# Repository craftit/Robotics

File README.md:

# Robotics
This is a general scratch area for my robotics projects. One things are in decent shape I will organise and move them more appropriate.

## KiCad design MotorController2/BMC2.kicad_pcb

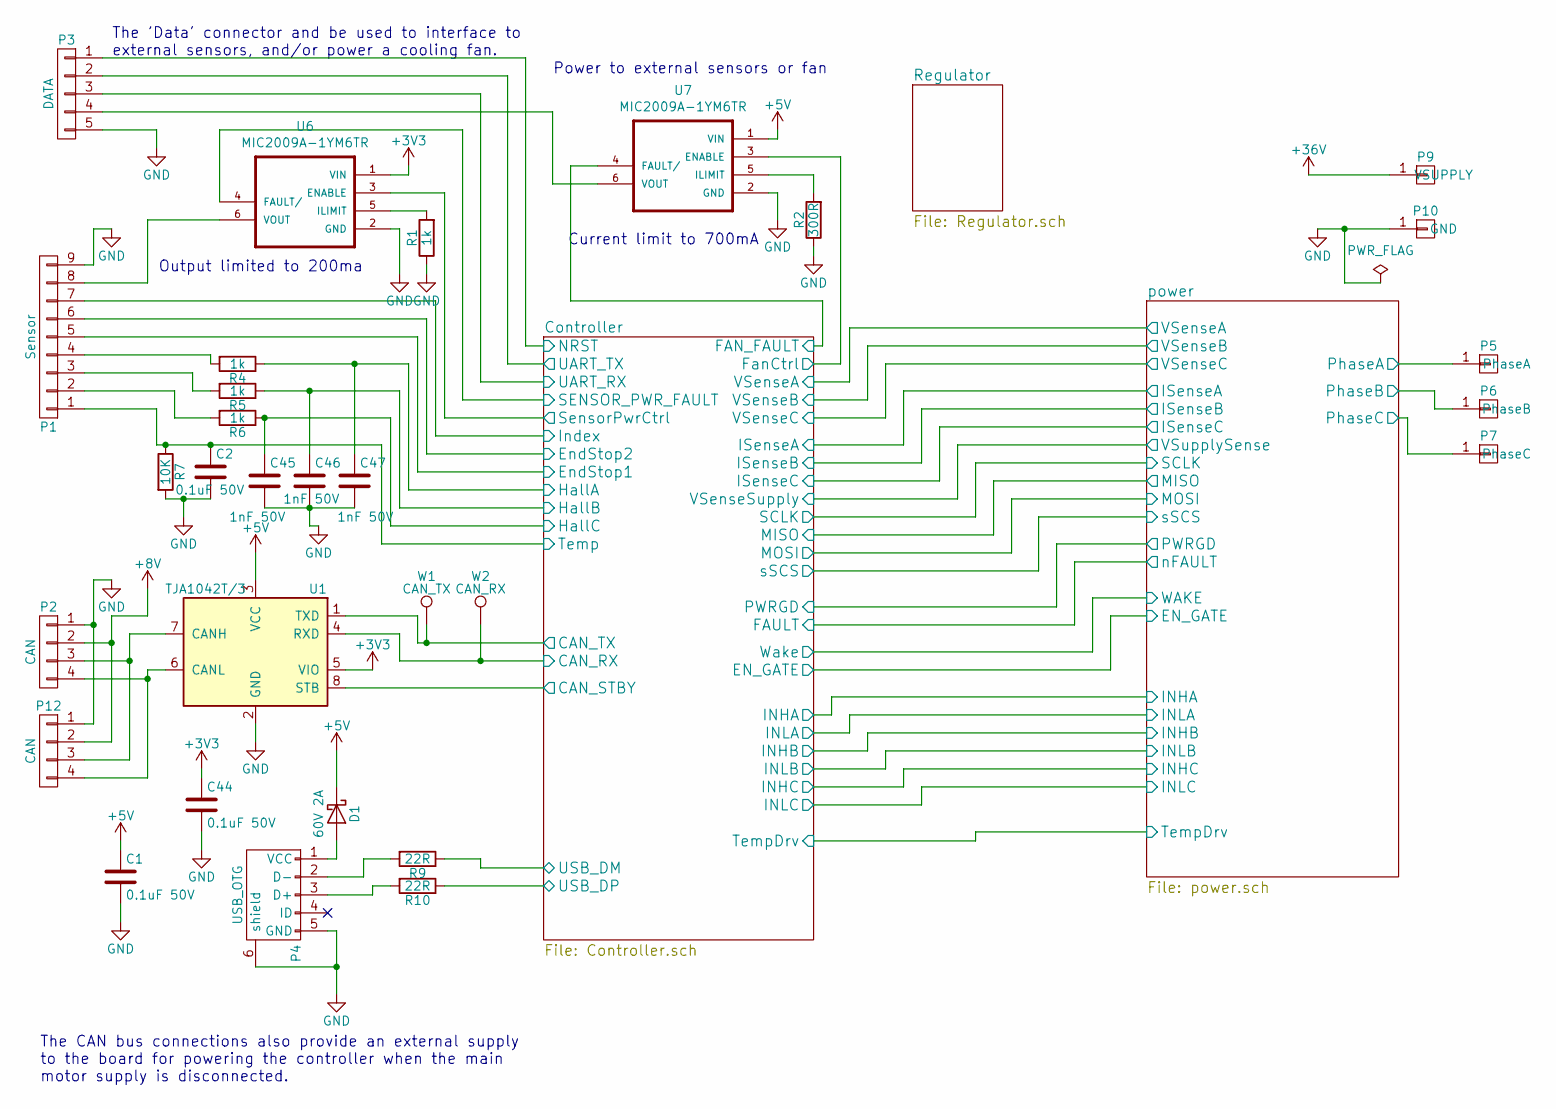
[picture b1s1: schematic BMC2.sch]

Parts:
C1: 0.1uF 50V; C_0805_HandSoldering; Farnell 1759265
C2, C44: 0.1uF 50V; C_0805_HandSoldering
C45, C46, C47: 1nF 50V; C_0805_HandSoldering; Farnell 9406344
D1: 60V 2A; SOD-123; Farnell 2284958
P1: Sensor; Pin_Header_Angled_1x09; Farnell 2468365
P2, P12: CAN; Pin_Header_Angled_1x04; Farnell 588738
P3: DATA; Pin_Header_Angled_1x05; Farnell 588740
P4: USB_OTG; USB_Mini-B; Farnell 1125348
P5: PhaseA; 1pin
P6: PhaseB; 1pin
P7: PhaseC; 1pin
P9: VSUPPLY; 1pin
P10: GND; 1pin
R1, R5, R6: 1k; R_0805_HandSoldering
R2: 300R; R_0805_HandSoldering; Farnell 2447633
R4: 1k; R_0805_HandSoldering; Farnell 2447587
R7: 10K; R_0805_HandSoldering; Farnell 2447553
R9: 22R; R_0805_HandSoldering; Farnell 2447609
R10: 22R; R_0805_HandSoldering
U1: TJA1042T/3; SOIC-8_3.9x4.9mm_Pitch1.27mm; Farnell 2574957
U6: MIC2009A-1YM6TR; SOT-23-6; Farnell 2509888
U7: MIC2009A-1YM6TR; SOT-23-6
W1: CAN_TX; Measurement_Point_Round-SMD-Pad_Small
W2: CAN_RX; Measurement_Point_Round-SMD-Pad_Small

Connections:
+3V3: C44.1, U1.5 (VIO), U6.1 (VIN); also elsewhere on the board
+5V: C1.1, D1.1 (K), U1.3 (VCC), U7.1 (VIN); also elsewhere on the board
+8V: P2.2, P12.2; also elsewhere on the board
+36V: P9.1; also elsewhere on the board
/Controller/CAN_RX: U1.4 (RXD), W2.1; also elsewhere on the board
/Controller/CAN_STBY: U1.8 (STB); also elsewhere on the board
/Controller/CAN_TX: U1.1 (TXD), W1.1; also elsewhere on the board
/Controller/EndStop1: P1.5; also elsewhere on the board
/Controller/EndStop2: P1.6; also elsewhere on the board
/Controller/FAN_FAULT: U7.4 (FAULT/); also elsewhere on the board
/Controller/FanCtrl: U7.3 (ENABLE); also elsewhere on the board
/Controller/HallA: C47.1, R4.1; also elsewhere on the board
/Controller/HallB: C46.1, R5.1; also elsewhere on the board
/Controller/HallC: C45.1, R6.1; also elsewhere on the board
/Controller/Index: P1.7; also elsewhere on the board
/Controller/SENSOR_PWR_FAULT: U6.4 (FAULT/); also elsewhere on the board
/Controller/SensorPwrCtrl: U6.3 (ENABLE); also elsewhere on the board
/Controller/Temp: C2.1, P1.1, R7.1; also elsewhere on the board
/Controller/UART_RX: P3.3; also elsewhere on the board
/Controller/UART_TX: P3.2; also elsewhere on the board
/Controller/USB_DM: R9.1; also elsewhere on the board
/Controller/USB_DP: R10.1; also elsewhere on the board
/power/PhaseA: P5.1; also elsewhere on the board
/power/PhaseB: P6.1; also elsewhere on the board
/power/PhaseC: P7.1; also elsewhere on the board
GND: C1.2, C2.2, C44.2, C45.2, C46.2, C47.2, P1.9, P2.1, P3.5, P4.5 (GND), P4.6 (shield), P10.1, P12.1, R1.1, R2.1, R7.2, U1.2 (GND), U6.2 (GND), U7.2 (GND); also elsewhere on the board
NRST: P3.1; also elsewhere on the board
unnamed: D1.2 (A), P4.1 (VCC)
unnamed: P1.2, R6.2
unnamed: P1.3, R5.2
unnamed: P1.4, R4.2
unnamed: P1.8, U6.6 (VOUT)
unnamed: P3.4, U7.6 (VOUT)
unnamed: P4.2 (D-), R9.2
unnamed: P4.3 (D+), R10.2
unnamed: P2.3, P12.3, U1.7 (CANH)
unnamed: P2.4, P12.4, U1.6 (CANL)
unnamed: R1.2, U6.5 (ILIMIT)
unnamed: R2.2, U7.5 (ILIMIT)

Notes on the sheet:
Output limited to 200ma
Current limit to 700mA
Power to external sensors or fan
The CAN bus connections also provide an external supply to the board for powering the controller when the main motor supply is disconnected.
The 'Data' connector and be used to interface to external sensors, and/or power a cooling fan.

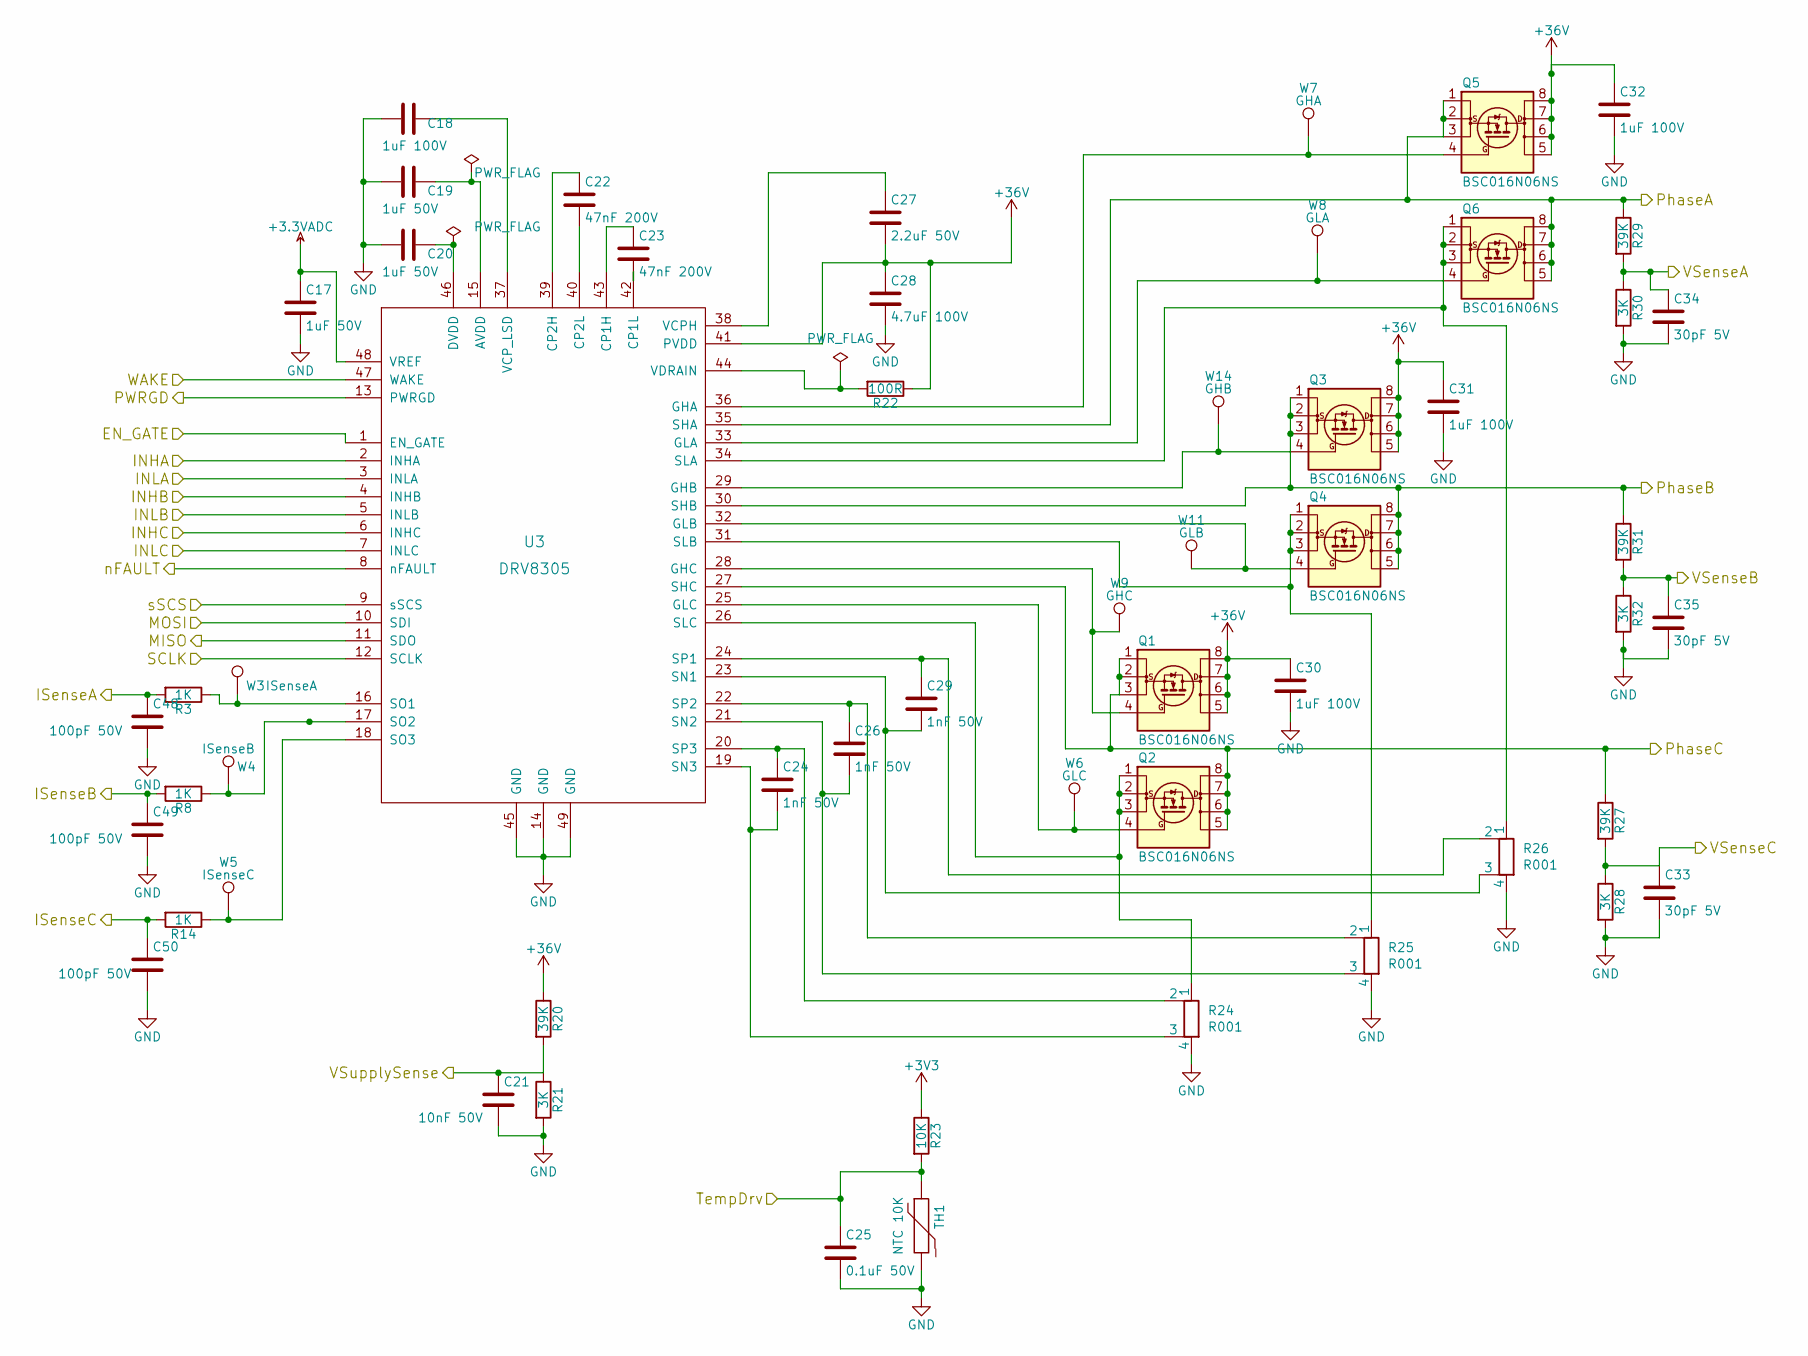
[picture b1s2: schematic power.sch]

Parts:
C17, C19, C20: 1uF 50V; C_0805_HandSoldering
C18, C30, C31, C32: 1uF 100V; C_1206_HandSoldering; Farnell 2320876
C21: 10nF 50V; C_0805_HandSoldering; Farnell 1414662
C22, C23: 47nF 200V; C_1206_HandSoldering; Farnell 1855874
C24, C26, C29: 1nF 50V; C_0805_HandSoldering; Farnell 9406344
C25: 0.1uF 50V; C_0805_HandSoldering
C27: 2.2uF 50V; C_1206_HandSoldering; Farnell 1288208
C28: 4.7uF 100V; C_1206_HandSoldering; Farnell 2310265
C33, C34, C35: 30pF 5V; C_0805_HandSoldering; Farnell 2581093
C48: 100pF 50V; C_0805_HandSoldering; Farnell 1759203
C49, C50: 100pF 50V; C_0805_HandSoldering
Q1, Q2, Q3, Q4, Q6: BSC016N06NS; SON127P532X615X110-8N
Q5: BSC016N06NS; SON127P532X615X110-8N; Farnell2 2432702
R3, R8, R14: 1K; R_0805_HandSoldering
R20, R27, R31: 39K; R_0805_HandSoldering
R21, R28, R32: 3K; R_0805_HandSoldering
R22: 100R; R_0805_HandSoldering; Farnell 2447552
R23: 10K; R_0805_HandSoldering
R24, R25: R001; R_PSR400_SENSE
R26: R001; R_PSR400_SENSE; Farnell 2475107
R29: 39K; R_0805_HandSoldering; Farnell 2447646
R30: 3K; R_0805_HandSoldering; Farnell 2073731
TH1: NTC 10K; R_0805_HandSoldering; Farnell 2103179
U3: DRV8305; QFP50P900X900X120-49N; Farnell 2611246
W3: ISenseA; Measurement_Point_Round-SMD-Pad_Small
W4: ISenseB; Measurement_Point_Round-SMD-Pad_Small
W5: ISenseC; Measurement_Point_Round-SMD-Pad_Small
W6: GLC; Measurement_Point_Round-SMD-Pad_Small
W7: GHA; Measurement_Point_Round-SMD-Pad_Small
W8: GLA; Measurement_Point_Round-SMD-Pad_Small
W9: GHC; Measurement_Point_Round-SMD-Pad_Small
W11: GLB; Measurement_Point_Round-SMD-Pad_Small
W14: GHB; Measurement_Point_Round-SMD-Pad_Small

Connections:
+3.3VADC: C17.1, U3.48 (VREF); also elsewhere on the board
+3V3: R23.1; also elsewhere on the board
+36V: C27.2, C28.1, C30.1, C31.1, C32.1, Q1.5 (D), Q1.6 (D), Q1.7 (D), Q1.8 (D), Q3.5 (D), Q3.6 (D), Q3.7 (D), Q3.8 (D), Q5.5 (D), Q5.6 (D), Q5.7 (D), Q5.8 (D), R20.1, R22.1, U3.41 (PVDD); also elsewhere on the board
/Controller/EN_GATE: U3.1 (EN_GATE); also elsewhere on the board
/Controller/FAULT: U3.8 (nFAULT); also elsewhere on the board
/Controller/INHA: U3.2 (INHA); also elsewhere on the board
/Controller/INHB: U3.4 (INHB); also elsewhere on the board
/Controller/INHC: U3.6 (INHC); also elsewhere on the board
/Controller/INLA: U3.3 (INLA); also elsewhere on the board
/Controller/INLB: U3.5 (INLB); also elsewhere on the board
/Controller/INLC: U3.7 (INLC); also elsewhere on the board
/Controller/ISenseA: C48.1, R3.2; also elsewhere on the board
/Controller/ISenseB: C49.1, R8.2; also elsewhere on the board
/Controller/ISenseC: C50.1, R14.2; also elsewhere on the board
/Controller/MISO: U3.11 (SDO); also elsewhere on the board
/Controller/MOSI: U3.10 (SDI); also elsewhere on the board
/Controller/PWRGD: U3.13 (PWRGD); also elsewhere on the board
/Controller/SCLK: U3.12 (SCLK); also elsewhere on the board
/Controller/TempDrv: C25.1, R23.2, TH1.1; also elsewhere on the board
/Controller/VSenseA: C34.1, R29.2, R30.1; also elsewhere on the board
/Controller/VSenseB: C35.1, R31.2, R32.1; also elsewhere on the board
/Controller/VSenseC: C33.1, R27.2, R28.1; also elsewhere on the board
/Controller/VSenseSupply: C21.1, R20.2, R21.1; also elsewhere on the board
/Controller/sSCS: U3.9 (sSCS); also elsewhere on the board
/power/PhaseA: Q5.1 (S), Q5.2 (S), Q5.3 (S), Q6.5 (D), Q6.6 (D), Q6.7 (D), Q6.8 (D), R29.1, U3.35 (SHA); also elsewhere on the board
/power/PhaseB: Q3.1 (S), Q3.2 (S), Q3.3 (S), Q4.5 (D), Q4.6 (D), Q4.7 (D), Q4.8 (D), R31.1, U3.30 (SHB); also elsewhere on the board
/power/PhaseC: Q1.1 (S), Q1.2 (S), Q1.3 (S), Q2.5 (D), Q2.6 (D), Q2.7 (D), Q2.8 (D), R27.1, U3.27 (SHC); also elsewhere on the board
/power/WAKE: U3.47 (WAKE); also elsewhere on the board
GND: C17.2, C18.2, C19.2, C20.2, C21.2, C25.2, C28.2, C30.2, C31.2, C32.2, C33.2, C34.2, C35.2, C48.2, C49.2, C50.2, R21.2, R24.4, R25.4, R26.4, R28.2, R30.2, R32.2, TH1.2, U3.14 (GND), U3.45 (GND), U3.49 (GND); also elsewhere on the board
unnamed: C18.1, U3.37 (VCP_LSD)
unnamed: C19.1, U3.15 (AVDD)
unnamed: C20.1, U3.46 (DVDD)
unnamed: C22.1, U3.39 (CP2H)
unnamed: C22.2, U3.40 (CP2L)
unnamed: C23.1, U3.43 (CP1H)
unnamed: C23.2, U3.42 (CP1L)
unnamed: C24.1, R24.2, U3.20 (SP3)
unnamed: C24.2, R24.3, U3.19 (SN3)
unnamed: C26.1, R25.2, U3.22 (SP2)
unnamed: C26.2, R25.3, U3.21 (SN2)
unnamed: C27.1, U3.38 (VCPH)
unnamed: C29.1, R26.2, U3.24 (SP1)
unnamed: C29.2, R26.3, U3.23 (SN1)
unnamed: Q1.4 (G), U3.28 (GHC), W9.1
unnamed: Q2.1 (S), Q2.2 (S), Q2.3 (S), R24.1, U3.26 (SLC)
unnamed: Q2.4 (G), U3.25 (GLC), W6.1
unnamed: Q3.4 (G), U3.29 (GHB), W14.1
unnamed: Q4.1 (S), Q4.2 (S), Q4.3 (S), R25.1, U3.31 (SLB)
unnamed: Q4.4 (G), U3.32 (GLB), W11.1
unnamed: Q5.4 (G), U3.36 (GHA), W7.1
unnamed: Q6.1 (S), Q6.2 (S), Q6.3 (S), R26.1, U3.34 (SLA)
unnamed: Q6.4 (G), U3.33 (GLA), W8.1
unnamed: R3.1, U3.16 (SO1), W3.1
unnamed: R8.1, U3.17 (SO2), W4.1
unnamed: R14.1, U3.18 (SO3), W5.1
unnamed: R22.2, U3.44 (VDRAIN)

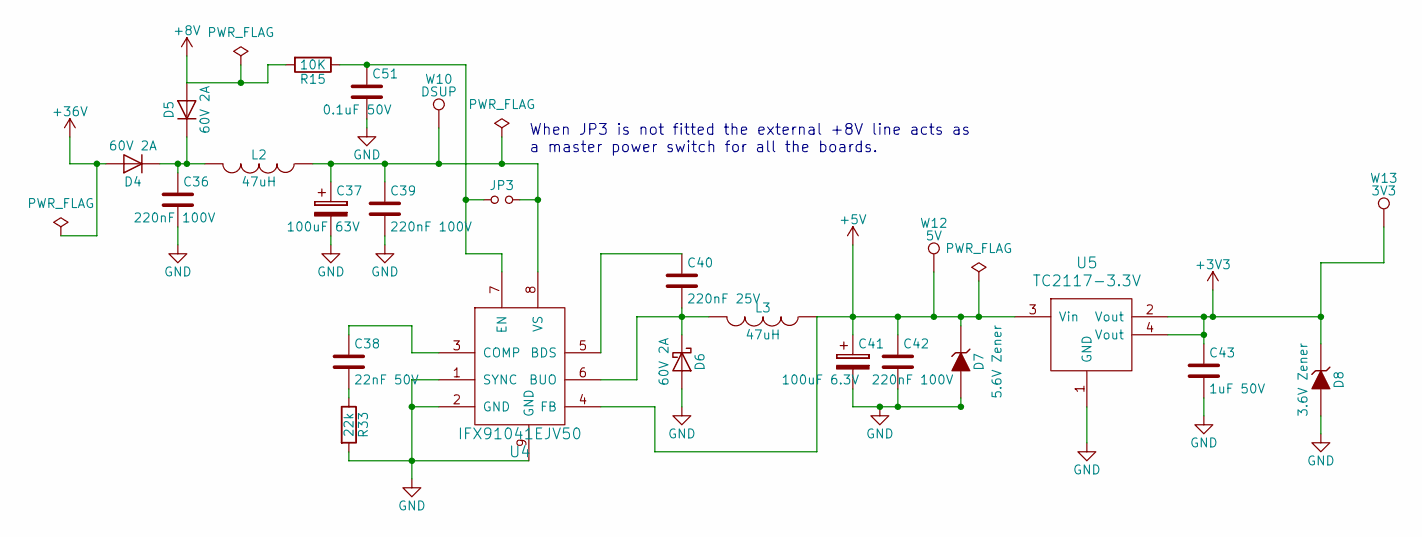
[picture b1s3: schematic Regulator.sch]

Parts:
C36, C39: 220nF 100V; C_1206_HandSoldering; Farnell 1856615
C37: 100uF 63V; c_elec_10x10.5; Farnell 9696040
C38: 22nF 50V; C_0805_HandSoldering; Farnell 1414682
C40: 220nF 25V; C_0805_HandSoldering; Farnell 1856615
C41: 100uF 6.3V; c_elec_6.3x5.8; Farnell 2611349
C42: 220nF 100V; C_0805_HandSoldering; Farnell 1856615
C43: 1uF 50V; C_0805_HandSoldering
C51: 0.1uF 50V; C_0805_HandSoldering
D4: 60V 2A; SOD-123
D5, D6: 60V 2A; SOD-123; Farnell 2284958
D7: 5.6V Zener; SOD-123; Part MMSZ4690T1G; Farnell 1459122
D8: 3.6V Zener; SOD-123; Part MMSZ5227B; Farnell 1700854
JP3: Jumper_NO_Small; R_0805_HandSoldering
L2: 47uH; SELF-WE-PD3S; Farnell 2345091
L3: 47uH; SELF-WE-PD3S
R15: 10K; R_0805_HandSoldering
R33: 22k; R_0805_HandSoldering; Farnell 9238646
U4: IFX91041EJV50; SOIC-8-1EP_3.9x4.9mm_Pitch1.27mm; Farnell 2432504
U5: TC2117-3.3V; SOT-223; Farnell 1605581
W10: DSUP; Measurement_Point_Round-SMD-Pad_Small
W12: 5V; Measurement_Point_Round-SMD-Pad_Small
W13: 3V3; Measurement_Point_Round-SMD-Pad_Small

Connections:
+3V3: C43.1, D8.1 (K), U5.2 (Vout), U5.4 (Vout), W13.1; also elsewhere on the board
+5V: C41.1, C42.1, D7.1 (K), L3.1, U4.4 (FB), U5.3 (Vin), W12.1; also elsewhere on the board
+8V: D5.2 (A), R15.2; also elsewhere on the board
+36V: D4.2 (A); also elsewhere on the board
GND: C36.2, C37.2, C39.2, C41.2, C42.2, C43.2, C51.2, D6.2 (A), D7.2 (A), D8.2 (A), R33.2, U4.1 (SYNC), U4.2 (GND), U4.9 (GND), U5.1 (GND); also elsewhere on the board
unnamed: C36.1, D4.1 (K), D5.1 (K), L2.2
unnamed: C37.1, C39.1, JP3.2, L2.1, U4.8 (VS), W10.1
unnamed: C38.1, U4.3 (COMP)
unnamed: C38.2, R33.1
unnamed: C40.1, U4.5 (BDS)
unnamed: C40.2, D6.1 (K), L3.2, U4.6 (BUO)
unnamed: C51.1, JP3.1, R15.1, U4.7 (EN)

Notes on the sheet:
When JP3 is not fitted the external +8V line acts as a master power switch for all the boards.

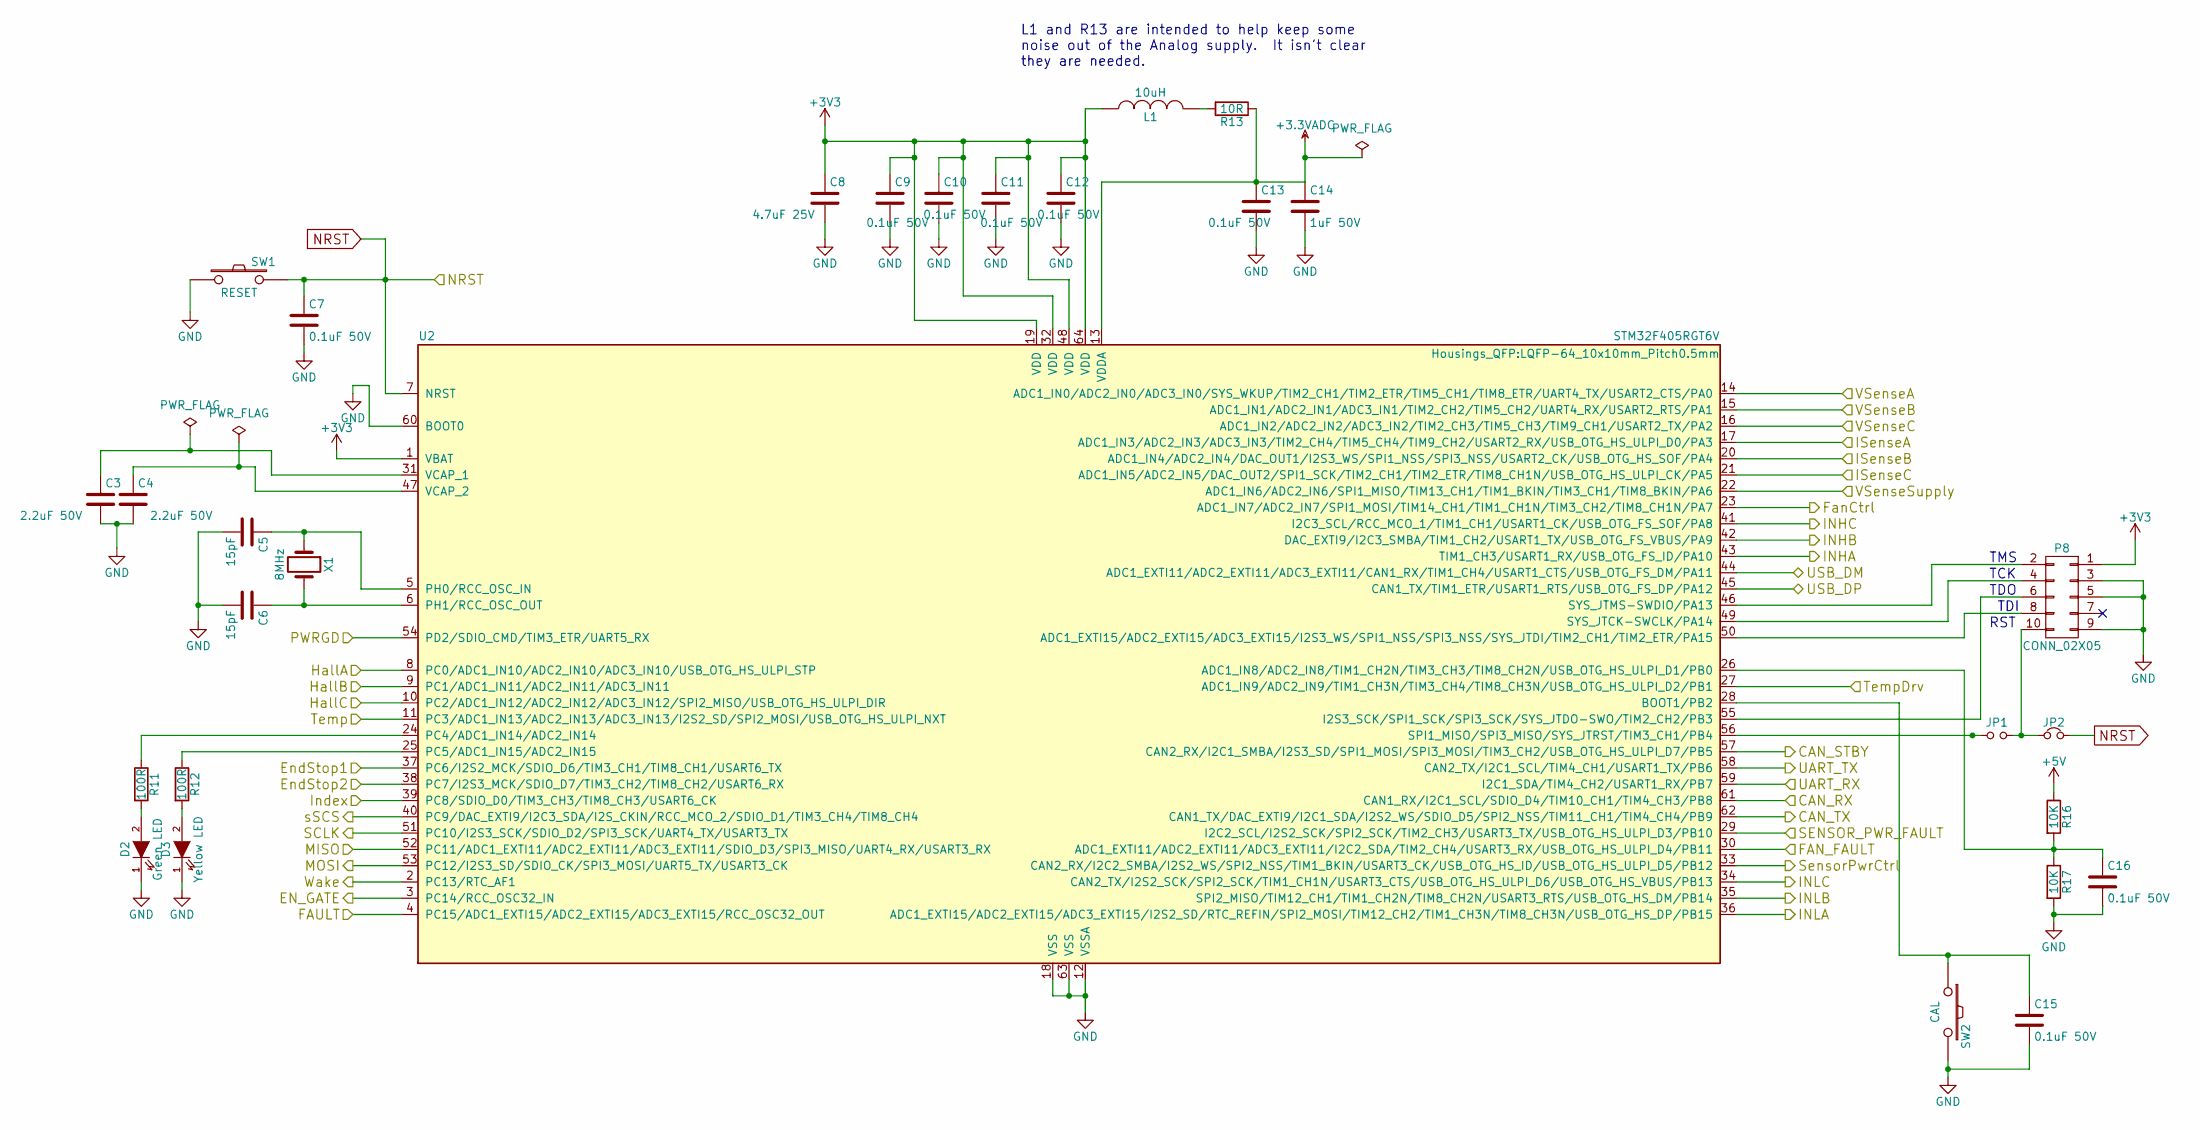
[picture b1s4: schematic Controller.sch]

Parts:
C3, C4: 2.2uF 50V; C_0805_HandSoldering; Farnell 2611933
C5: 15pF; C_0805_HandSoldering; Farnell 2497014
C6: 15pF; C_0805_HandSoldering
C7, C9, C10, C11, C12, C13, C15, C16: 0.1uF 50V; C_0805_HandSoldering
C8: 4.7uF 25V; C_1206_HandSoldering; Farnell 9227938
C14: 1uF 50V; C_0805_HandSoldering; Farnell 1759432
D2: Green LED; LED_0805; Farnell 1465996
D3: Yellow LED; LED_0805; Farnell 1581241
JP1: Jumper_NO_Small; R_0805_HandSoldering
JP2: Jumper_NC_Small; R_0805_HandSoldering; Farnell 9333681
L1: 10uH; R_0805_HandSoldering; Farnell 2215650
P8: CONN_02X05; SMT-HDR-10
R11, R12: 100R; R_0805_HandSoldering
R13: 10R; R_0805_HandSoldering; Farnell 2447556
R16, R17: 10K; R_0805_HandSoldering
SW1: RESET; SW_SPST_FSMSM; Farnell 2468741
SW2: CAL; SW_SPST_FSMSM; Farnell 2468741
U2: STM32F405RGT6V; LQFP-64_10x10mm_Pitch0.5mm; Farnell 2333282
X1: 8MHz; ABM3; Farnell 2101329

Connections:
+3.3VADC: C13.1, C14.1, R13.1, U2.13 (VDDA); also elsewhere on the board
+3V3: C8.1, C9.1, C10.1, C11.1, C12.1, L1.1, P8.1, U2.1 (VBAT), U2.19 (VDD), U2.32 (VDD), U2.48 (VDD), U2.64 (VDD); also elsewhere on the board
+5V: R16.1; also elsewhere on the board
/Controller/CAN_RX: U2.61 (CAN1_RX/I2C1_SCL/SDIO_D4/TIM10_CH1/TIM4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); also elsewhere on the board
/Controller/CAN_STBY: U2.57 (CAN2_RX/I2C1_SMBA/I2S3_SD/SPI1_MOSI/SPI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); also elsewhere on the board
/Controller/CAN_TX: U2.62 (CAN1_TX/DAC_EXTI9/I2C1_SDA/I2S2_WS/SDIO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); also elsewhere on the board
/Controller/EN_GATE: U2.3 (PC14/RCC_OSC32_IN); also elsewhere on the board
/Controller/EndStop1: U2.37 (PC6/I2S2_MCK/SDIO_D6/TIM3_CH1/TIM8_CH1/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); also elsewhere on the board
/Controller/EndStop2: U2.38 (PC7/I2S3_MCK/SDIO_D7/TIM3_CH2/TIM8_CH2/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); also elsewhere on the board
/Controller/FAN_FAULT: U2.30 (ADC1_EXTI11/ADC2_EXTI11/ADC3_EXTI11/I2C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); also elsewhere on the board
/Controller/FAULT: U2.4 (PC15/ADC1_EXTI15/ADC2_EXTI15/ADC3_EXTI1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); also elsewhere on the board
/Controller/FanCtrl: U2.23 (ADC1_IN7/ADC2_IN7/SPI1_MOSI/TIM14_CH1/T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); also elsewhere on the board
/Controller/HallA: U2.8 (PC0/ADC1_IN10/ADC2_IN10/ADC3_IN10/USB_O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); also elsewhere on the board
/Controller/HallB: U2.9 (PC1/ADC1_IN11/ADC2_IN11/ADC3_IN11); also elsewhere on the board
/Controller/HallC: U2.10 (PC2/ADC1_IN12/ADC2_IN12/ADC3_IN12/SPI2_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); also elsewhere on the board
/Controller/INHA: U2.43 (TIM1_CH3/USART1_RX/USB_OTG_FS_ID/PA10); also elsewhere on the board
/Controller/INHB: U2.42 (DAC_EXTI9/I2C3_SMBA/TIM1_CH2/USART1_TX/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); also elsewhere on the board
/Controller/INHC: U2.41 (I2C3_SCL/RCC_MCO_1/TIM1_CH1/USART1_CK/U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); also elsewhere on the board
/Controller/INLA: U2.36 (ADC1_EXTI15/ADC2_EXTI15/ADC3_EXTI15/I2S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); also elsewhere on the board
/Controller/INLB: U2.35 (SPI2_MISO/TIM12_CH1/TIM1_CH2N/TIM8_CH2N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); also elsewhere on the board
/Controller/INLC: U2.34 (CAN2_TX/I2S2_SCK/SPI2_SCK/TIM1_CH1N/USA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); also elsewhere on the board
/Controller/ISenseA: U2.17 (ADC1_IN3/ADC2_IN3/ADC3_IN3/TIM2_CH4/TIM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); also elsewhere on the board
/Controller/ISenseB: U2.20 (ADC1_IN4/ADC2_IN4/DAC_OUT1/I2S3_WS/SPI1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); also elsewhere on the board
/Controller/ISenseC: U2.21 (ADC1_IN5/ADC2_IN5/DAC_OUT2/SPI1_SCK/TIM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); also elsewhere on the board
/Controller/Index: U2.39 (PC8/SDIO_D0/TIM3_CH3/TIM8_CH3/USART6_CK); also elsewhere on the board
/Controller/MISO: U2.52 (PC11/ADC1_EXTI11/ADC2_EXTI11/ADC3_EXTI1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); also elsewhere on the board
/Controller/MOSI: U2.53 (PC12/I2S3_SD/SDIO_CK/SPI3_MOSI/UART5_TX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); also elsewhere on the board
/Controller/PWRGD: U2.54 (PD2/SDIO_CMD/TIM3_ETR/UART5_RX); also elsewhere on the board
/Controller/SCLK: U2.51 (PC10/I2S3_SCK/SDIO_D2/SPI3_SCK/UART4_TX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); also elsewhere on the board
/Controller/SENSOR_PWR_FAULT: U2.29 (I2C2_SCL/I2S2_SCK/SPI2_SCK/TIM2_CH3/USA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); also elsewhere on the board
/Controller/SensorPwrCtrl: U2.33 (CAN2_RX/I2C2_SMBA/I2S2_WS/SPI2_NSS/TIM1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); also elsewhere on the board
/Controller/Temp: U2.11 (PC3/ADC1_IN13/ADC2_IN13/ADC3_IN13/I2S2_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); also elsewhere on the board
/Controller/TempDrv: U2.27 (ADC1_IN9/ADC2_IN9/TIM1_CH3N/TIM3_CH4/TI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); also elsewhere on the board
/Controller/UART_RX: U2.59 (I2C1_SDA/TIM4_CH2/USART1_RX/PB7); also elsewhere on the board
/Controller/UART_TX: U2.58 (CAN2_TX/I2C1_SCL/TIM4_CH1/USART1_TX/PB6); also elsewhere on the board
/Controller/USB_DM: U2.44 (ADC1_EXTI11/ADC2_EXTI11/ADC3_EXTI11/CAN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); also elsewhere on the board
/Controller/USB_DP: U2.45 (CAN1_TX/TIM1_ETR/USART1_RTS/USB_OTG_FS_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); also elsewhere on the board
/Controller/VSenseA: U2.14 (ADC1_IN0/ADC2_IN0/ADC3_IN0/SYS_WKUP/TIM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); also elsewhere on the board
/Controller/VSenseB: U2.15 (ADC1_IN1/ADC2_IN1/ADC3_IN1/TIM2_CH2/TIM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); also elsewhere on the board
/Controller/VSenseC: U2.16 (ADC1_IN2/ADC2_IN2/ADC3_IN2/TIM2_CH3/TIM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); also elsewhere on the board
/Controller/VSenseSupply: U2.22 (ADC1_IN6/ADC2_IN6/SPI1_MISO/TIM13_CH1/T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); also elsewhere on the board
/Controller/sSCS: U2.40 (PC9/DAC_EXTI9/I2C3_SDA/I2S_CKIN/RCC_MCO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); also elsewhere on the board
/power/WAKE: U2.2 (PC13/RTC_AF1); also elsewhere on the board
GND: C3.2, C4.2, C5.2, C6.2, C7.2, C8.2, C9.2, C10.2, C11.2, C12.2, C13.2, C14.2, C15.2, C16.2, D2.1 (K), D3.1 (K), P8.3, P8.5, P8.9, R17.2, SW1.1, SW2.2, U2.12 (VSSA), U2.18 (VSS), U2.60 (BOOT0), U2.63 (VSS); also elsewhere on the board
NRST: C7.1, JP2.2, SW1.2, U2.7 (NRST); also elsewhere on the board
unnamed: C3.1, U2.31 (VCAP_1)
unnamed: C4.1, U2.47 (VCAP_2)
unnamed: C5.1, U2.5 (PH0/RCC_OSC_IN), X1.1
unnamed: C6.1, U2.6 (PH1/RCC_OSC_OUT), X1.2
unnamed: C15.1, SW2.1, U2.28 (BOOT1/PB2)
unnamed: C16.1, R16.2, R17.1, U2.26 (ADC1_IN8/ADC2_IN8/TIM1_CH2N/TIM3_CH3/TI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)
unnamed: D2.2 (A), R11.2
unnamed: D3.2 (A), R12.2
unnamed: JP1.1, U2.56 (SPI1_MISO/SPI3_MISO/SYS_JTRST/TIM3_CH1/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)
unnamed: JP1.2, JP2.1, P8.10
unnamed: L1.2, R13.2
unnamed: P8.2, U2.46 (SYS_JTMS-SWDIO/PA13)
unnamed: P8.4, U2.49 (SYS_JTCK-SWCLK/PA14)
unnamed: P8.6, U2.55 (I2S3_SCK/SPI1_SCK/SPI3_SCK/SYS_JTDO-SWO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)
unnamed: P8.8, U2.50 (ADC1_EXTI15/ADC2_EXTI15/ADC3_EXTI15/I2S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)
unnamed: R11.1, U2.24 (PC4/ADC1_IN14/ADC2_IN14)
unnamed: R12.1, U2.25 (PC5/ADC1_IN15/ADC2_IN15)

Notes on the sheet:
TMS
TCK
TDO
TDI
RST
L1 and R13 are intended to help keep some noise out of the Analog supply. It isn't clear they are needed.

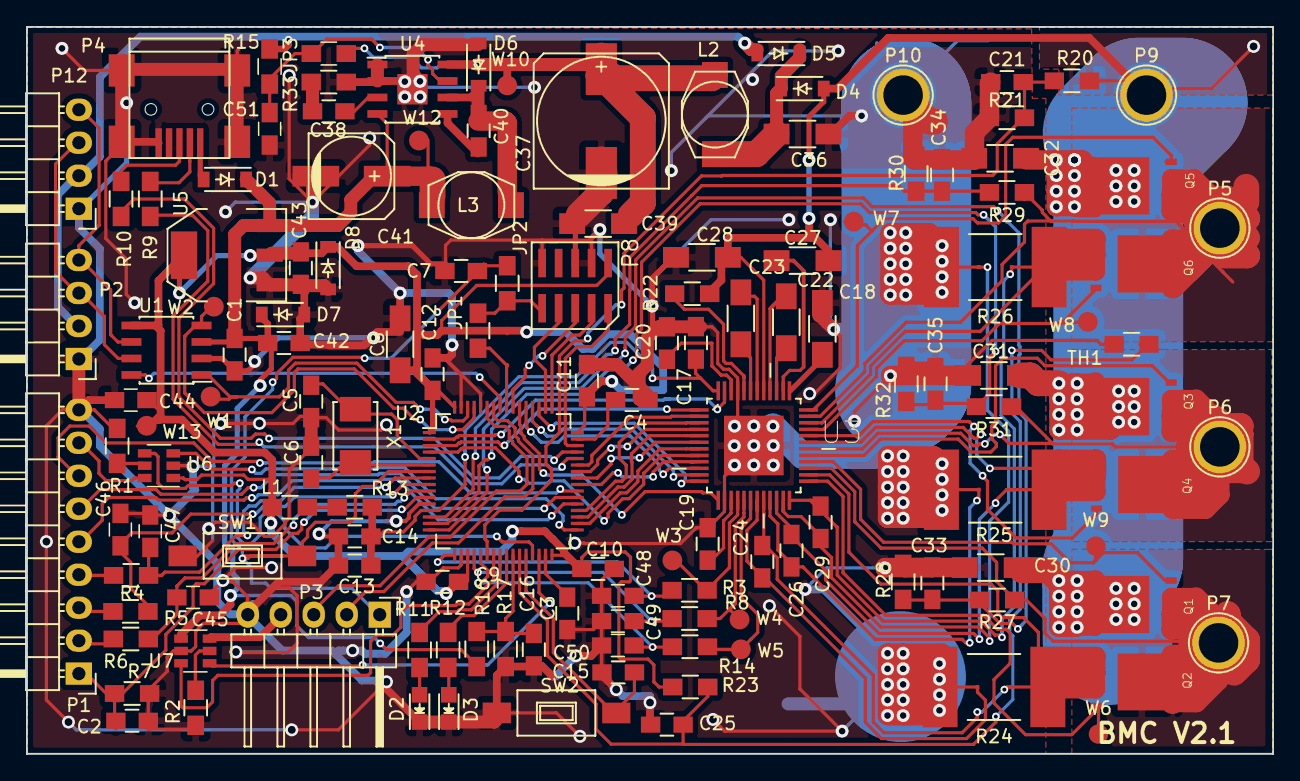
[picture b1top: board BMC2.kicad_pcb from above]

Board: 2 copper layers, 96.0 x 56.0 mm, 136 parts (0 on the bottom side), 113 nets.

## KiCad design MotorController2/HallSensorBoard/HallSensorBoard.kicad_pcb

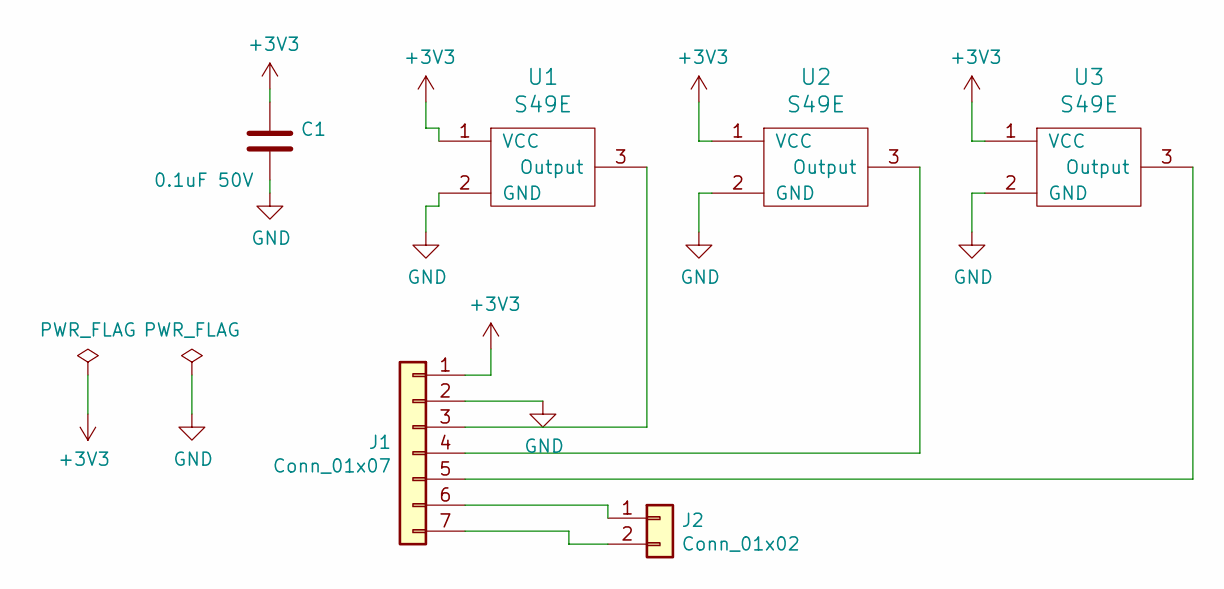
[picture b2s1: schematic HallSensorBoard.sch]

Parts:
C1: 0.1uF 50V; C_0805_HandSoldering
J1: Conn_01x07; Pin_Header_Angled_1x07_Pitch2.54mm
J2: Conn_01x02; Pin_Header_Straight_1x02_Pitch2.54mm
U1, U2, U3: S49E; TO-92_Inline_Narrow_Oval

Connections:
+3V3: C1.1, J1.1, U1.1 (VCC), U2.1 (VCC), U3.1 (VCC)
GND: C1.2, J1.2, U1.2 (GND), U2.2 (GND), U3.2 (GND)
unnamed: J1.3, U1.3 (Output)
unnamed: J1.4, U2.3 (Output)
unnamed: J1.5, U3.3 (Output)
unnamed: J1.6, J2.1
unnamed: J1.7, J2.2

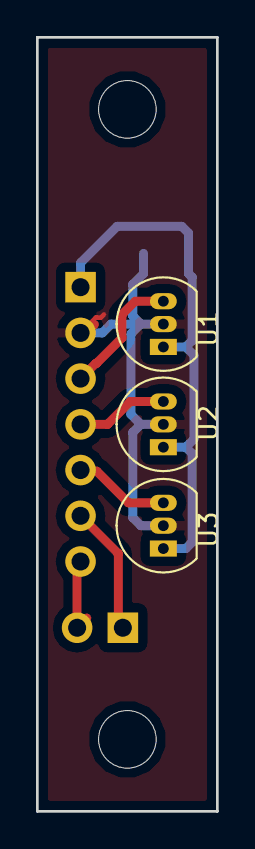
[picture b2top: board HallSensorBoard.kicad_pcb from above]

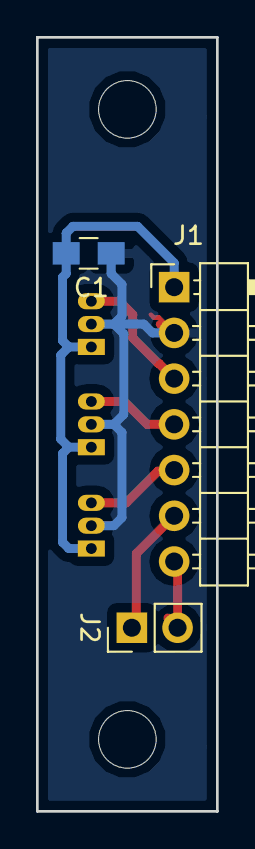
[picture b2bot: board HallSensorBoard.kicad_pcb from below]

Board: 2 copper layers, 10.0 x 43.0 mm, 6 parts (3 on the bottom side), 7 nets.

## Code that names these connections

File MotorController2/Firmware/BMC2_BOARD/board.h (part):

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/*
 * GPIOA setup:
 *
 * PA0  - VSENSEA                   (analog in)
 * PA1  - VSENSEB                   (analog in)
 * PA2  - VSENSEC                   (analog in)
 * PA3  - ISENSEA                   (analog in)
 * PA4  - ISENSEB                   (analog in)
 * PA5  - ISENSEC                   (analog in)
 * PA6  - VSUPPLY                   (analog in)
 * PA7  - NC                        (input pull-up)
 * PA8  - INHC                      (output push-pull)
 * PA9  - INHB                      (output push-pull)
 * PA10 - INHA                      (output push-pull)
 * PA11 - OTG_FS_DM                 (alternate 10).
 * PA12 - OTG_FS_DP                 (alternate 10).
 * PA13 - SWDIO                     (alternate 0).
 * PA14 - SWCLK                     (alternate 0).
 * PA15 - JTDI                      (?).
 */
#define VAL_GPIOA_MODER             (PIN_MODE_ANALOG(GPIOA_PIN0) |           \
                                     PIN_MODE_ANALOG(GPIOA_PIN1) |           \
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/*
 * GPIOB setup:
 *
 * PB0  - 5V MONITOR                (analog in).
 * PB1  - TEMP DRV                  (analog in).
 * PB2  - BUTTON                    (input pullup).
 * PB3  - SWO                       (alternate 0).
 * PB4  - JTRST (Option)            (input pullup).
 * PB5  - CAN_STBY                  (output).
 * PB6  - USART1_TX                 (alternate ?).
 * PB7  - USART1_RX                 (alternate ?).
 * PB8  - CAN_TX                    (alternate ?).
 * PB9  - CAN_RX                    (alternate ?).
 * PB10 - I2C_SCL/USART3_TX         (input pullup).
 * PB11 - I2C_SDA/USART3_RX         (input pullup).
 * PB12 - W14                       (output).
 * PB13 - INLC                      (output).
 * PB14 - INLB                      (output).
 * PB15 - INLA                      (output).
 */
#define VAL_GPIOB_MODER             (PIN_MODE_ANALOG(GPIOB_PIN0) |           \
                                     PIN_MODE_ANALOG(GPIOB_PIN1) |           \
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/*
 * GPIOC setup:
 *
 * PC0  - HALLA                     (analog in).
 * PC1  - HALLB                     (analog in).
 * PC2  - HALLC                     (analog in).
 * PC3  - TEMP                      (analog in).
 * PC4  - LED_GREEN                 (output).
 * PC5  - LED_YELLOW                (output).
 * PC6  - ENDSTOP1                  (input pullup).
 * PC7  - ENDSTOP2                  (input pullup).
 * PC8  - INDEX                     (input pullup).
 * PC9  - sSCS                      (output).
 * PC10 - SCLK                      (x).
 * PC11 - MISO                      (x).
 * PC12 - MOSI                      (x).
 * PC13 - WAKE                      (output).
 * PC14 - EN_GATE                   (output).
 * PC15 - FAULT                     (input pullup).
 */
#define VAL_GPIOC_MODER             (PIN_MODE_ANALOG(GPIOC_PIN0) |           \
                                     PIN_MODE_ANALOG(GPIOC_PIN1) |           \
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 *
 * PD0  - PIN0                      (input pullup).
 * PD1  - PIN1                      (input pullup).
 * PD2  - PWRGD                     (input pullup).
 * PD3  - PIN3                      (input pullup).
 * PD4  - PIN4                      (input pullup).
 * PD5  - PIN5                      (input pullup).
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/*
 * GPIOH setup:
 *
 * PH0  - OSC_IN                    (input floating).
 * PH1  - OSC_OUT                   (input floating).
 * PH2  - PIN2                      (input pullup).
 * PH3  - PIN3                      (input pullup).
 * PH4  - PIN4                      (input pullup).
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
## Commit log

2016-04-22 Add an initial version of the end plate.
2016-04-23 Add new parts.
2016-05-08 Add initial schematic for motor controller.
2016-05-14 Add a calibration object for hole sizes.
2016-05-30 Board layed out.
2016-05-30 Finished version 1.
2016-06-06 Updates.
2016-06-08 Add switching sequences.
2016-06-13 Added some interrupt handling.
2016-06-13 Set up of ADC.
2016-07-18 Stuff.
2016-07-19 More stl files.
2016-07-22 New parts.
2016-07-22 More updates.
2016-07-25 Fix constraints.
2016-07-25 Sort out files into the two different designs.
2016-07-29 New stl files.
2016-08-06 Initial end piece.
2016-08-06 New linear actuator.
2016-08-07 Add places for sensors.
2016-08-07 Make sensor holes smaller.
2016-08-13 Tweek sensor position
2016-08-13 Add stl files.
2016-09-08 Add parts for new gearbox.
2016-10-08 More parts.
2016-10-10 Starting to fit together.
2016-10-13 Add stl's of sun and planet gears.
2016-10-16 Motor turning.
2016-10-21 Using faster atan2 to avoid timing issues.
2016-10-23 Improved motor timing.
2016-10-23 More stuff.
2016-10-23 Add MT5208 motor mount.
2016-10-23 Add hip adaptor.
2016-10-25 Start work on new servo design.
2016-10-25 Base version of current servo.
2016-10-25 Some more current servo parts.
2016-10-25 New gearbox design.
2016-10-27 Working test bearing.
2016-10-28 Updated bearing to 40mm radius
2016-10-28 New carrier design.
2016-10-29 More fixes.
2016-10-30 Fixes for the carrier.
2016-11-02 Lots of fixes and updates.
2016-11-04 Start work on knee.
2016-11-08 Latest.
2016-11-12 Knee working.
2016-11-12 Added hip2.
2016-11-12 Fixed hip.
2016-11-13 Fix magnet removal slot.
2016-11-16 Wider hip joint.
2016-11-19 Fix push rod tails, and add notch to lower knee.
2016-11-22 Where we're at.
2016-11-22 Clean up.
2016-12-24 Work on new motor controller.
2016-12-31 Most of new motor controller schematic, and leg V2.
2017-01-04 Initial schematic complete.
2017-01-04 Component footprints.
2017-01-05 Design tweeks.
2017-01-05 Add local library.
2017-01-05 Work on PCB layout.
2017-01-10 Laying out power section.
2017-01-13 More of the layout done.
2017-01-13 More tweaks
2017-01-15 Layout nearly complete.
2017-01-15 Tweaks.
2017-01-16 Put in Champers for screws.
2017-01-16 About to change via drill size.
2017-01-16 Nearly there.
2017-01-16 Fixes for soldermask clearences
2017-01-22 Make tool hole a little bigger.
2017-01-22 Remove obsolete parts.
2017-01-22 Add 3 hall sensor mount.
2017-01-23 Add pelvis and refine motor mount.
2017-01-24 Add TODO list.
2017-01-25 Add body brackets.
2017-01-26 Add bumper to body bracket.
2017-01-27 Work on BOM.
2017-01-27 Add some vias
2017-01-28 Fix UpperKnee race.
2017-02-02 Tweaks to PCB.
2017-02-02 Make holes more recessed.
2017-02-12 Started on firmware.
2017-02-15 We have a USB device.
2017-02-16 Have a terminal up and running as well as adc.
2017-02-20 Some progress.
2017-02-20 More testing.
2017-02-27 A bit more work on wire wiggling.
2017-03-04 Move firmware into its own repo.
2017-05-08 Add new hip reinforcement with holes for the motor controller mount.
2017-05-15 Update end stop to be a ring.
2017-09-21 BMCV2.1 updates.
2017-09-22 Add power off option.
2017-09-22 Start on sensor board layout.
2017-09-22 Start on board outline.
2017-09-22 Final board.
2017-09-22 Board layouts as ordered.
2017-11-01 Updates for parts list.
2017-11-01 Update part number.
2017-11-29 Add index sensor plug.
2017-12-07 Add some annotations.

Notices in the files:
MotorController2/Firmware/BMC2_BOARD/board.h:
ChibiOS - Copyright (C) 2006..2016 Giovanni Di Sirio
Licensed under the Apache License, Version 2.0 (the "License");
